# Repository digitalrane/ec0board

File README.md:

ec0board
========

ec0board is a personal project to replace the dead control board in my otherwise landfill Kogan TKL mechanical keyboard.
It was designed to occupy the exact same physical dimensions, and have the exact same key switch spacing as the original board, however has a much more powerful user-controlled MCU.
The MCU used is an AT90USB1286, chosen for the number of GPIOs, enabling NKRO to be achieved. It uses a diode matrix to connect the key switches, and takes Cherry-MX compatible key switches (I use browns).
Support is being added to the open source QMK firmware for this board, as the intention is to run a completely open keyboard replacement.

The board supports a switchable backlight, and additional RGB LED underneath the board (to see if the controller is alive, basically) and switchable backlights for the Fn, Caps, Scroll and Num lock keys independently to the main backlight.

This board uses custom footprints and 3d models for the following. If you find any of them missing from this repository, please file an issue.
* Cherry MX Brown switch model and footprint
* AT90USB1286 model and footprint
* Ingwaz rune (because I like to ensure runes or sigils cover my electronics for great ~ mystical power ~)

Versions
========

* v0: Original prototype, ended up not working reliably because I goofed the electron-herding aspects of this version.
* v1: Original replacement. Found the Micro USB connector to be flimsy, because Micro USB is a bit crap. Also had a testing RGB LED space,
  which never worked right. Other than that, fairly reliable, but still relied on the Kogan TKL or similar cheap Aliexpress/eBay donor KB.
* v2: Never released or manufactured, added standalone supports, rerouted entire keyboard to use newly added standard KiCad key switch
  footprints, generally cleaned up routing. Started moving toward a Mini USB connector to address connector stability.
* v3: Decided to use USB-C during a dream, so rewired the whole power supply and USB connection section. Further routing improvements.
  Cleaned up all footprints, values, and added better more descriptive values to components so a proper BOM could be generated. Generated a
  proper BOM with the Interactive HTML BOM KiCad plugin. Updated everything for KiCad 5.1 and added some more 3D models. All required
  libraries are now in KiCad or this repo.

Firmware
========

This keyboard uses QMK, and a board definition and configuration is included in the `qmk_ec0board` directory. Drop this into QMK and set
your keyboard type to 'ec0board' on the make commandline as documented [here](https://beta.docs.qmk.fm/detailed-guides/getting_started_make_guide).

e.g.:
`make ec0board`

Flashing
========

Programming of the firmware is done via the ISP header. You will need a standard AVR ISP programmer, I use an Olimex unit. They keyboard
should not be powered via USB whilst flashing, but you won't get magic smoke if you do it accidentally (yeah I tried it, so what, are you a
cop?).

Fuses
=====

The fuses on your AT90USB1286 should be set for external crystal oscillator operation, with JTAG disabled, to free up enough GPIOs. We
also want SPIEN set so we can use the ISP to flash/recover the chip.

The fules should be set to -
(E:F3, H:D9, L:DE)

BOM
===

Thanks to the wonderful [InteractiveHtmlBom](https://github.com/openscopeproject/InteractiveHtmlBom) KiCad plugin, this repository now
contains a really nice HTML BOM. You can clone this repo and browse it locally in the `bom` directory, or download/view it from
[here](https://rawcdn.githack.com/devec0/ec0board/master/bom/ibom.html).

For U1, AT90USB1286 is the sensible option, because no keyboard needs the host mode support of AT90USB1287.
If you need host mode, you're an absolute maniac. I want to know what you're up to, get in touch!

TODO
====

* Finish code for lighting backlight behind Capslock, Scrolllock, Numlock and the Function key when engaged
* Finish code to get the Function key working correctly

And another thing
=================

<3

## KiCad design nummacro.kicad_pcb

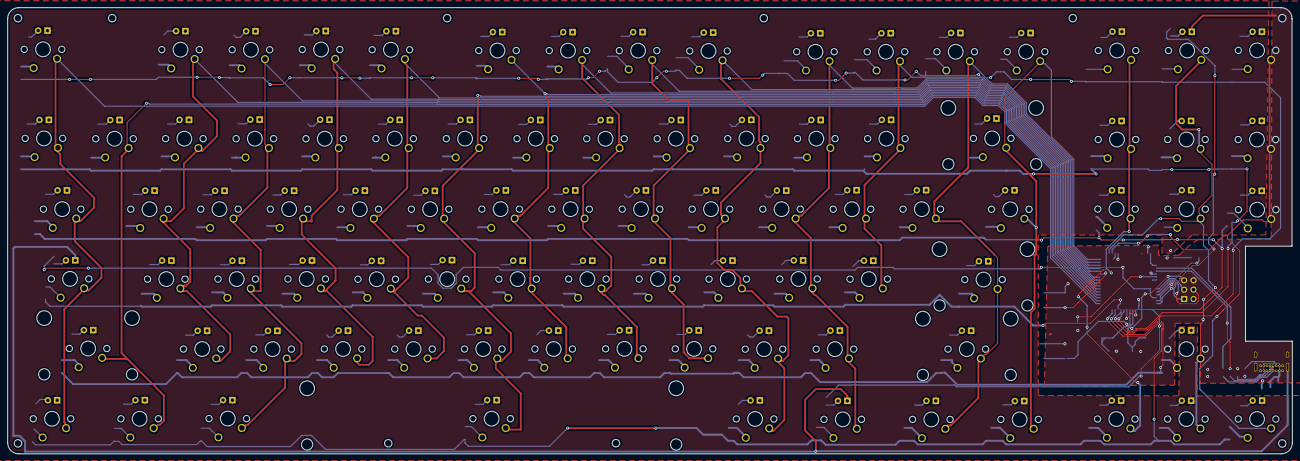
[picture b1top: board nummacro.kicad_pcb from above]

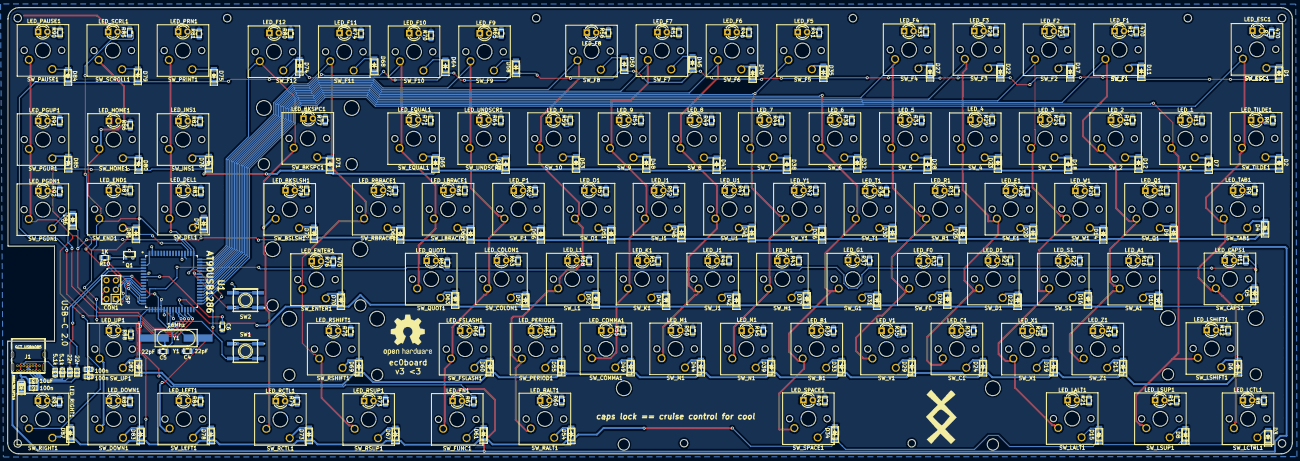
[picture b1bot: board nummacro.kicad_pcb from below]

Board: 2 copper layers, 348.1 x 120.9 mm, 368 parts (194 on the bottom side), 221 nets.

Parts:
C2, C3, C7: 100n; C_0805_2012Metric_Pad1.15x1.40mm_HandSolder
C4, C5: 22pF; C_0805_2012Metric_Pad1.15x1.40mm_HandSolder
C6: 1uF; C_0805_2012Metric_Pad1.15x1.40mm_HandSolder
C8: 10uF; C_0805_2012Metric_Pad1.15x1.40mm_HandSolder
CON1: ISP; PinHeader_2x03_P2.54mm_Vertical
D1, D2, D3, D4, D5, D6, D7, D8, D9, D10, D11, D12, D13, D14, D15, D16, D17, D18, D19, D20, D21, D22, D23, D24, D25, D26, D27, D28, D29, D30, D31, D32, D33, D34, D35, D36, D37, D38, D39, D40, D41, D42, D43, D44, D45, D46, D47, D48, D49, D50, D51, D52, D53, D54, D55, D56, D57, D58, D59, D60, D61, D62, D63, D64, D65, D66, D67, D68, D69, D70, D71, D72, D73, D74, D75, D76, D77, D78, D79, D80, D81, D82, D83, D84, D85, D86, D87: D; D_MiniMELF
D88: MBR130LSFT1G; D_PowerDI-123
J1: GCT USB4085; USB_C_Receptacle_GCT_USB4085
LED_0, LED_1, LED_2, LED_3, LED_4, LED_5, LED_6, LED_7, LED_8, LED_9: Led_Small; LED_D3.0mm
LED_A1: Led_Small; LED_D3.0mm
LED_B1: Led_Small; LED_D3.0mm
LED_BKSLSH1: Led_Small; LED_D3.0mm
LED_BKSPC1: Led_Small; LED_D3.0mm
LED_C1: Led_Small; LED_D3.0mm
LED_CAPS1: Led_Small; LED_D3.0mm
LED_COLON1: Led_Small; LED_D3.0mm
LED_COMMA1: Led_Small; LED_D3.0mm
LED_D1: Led_Small; LED_D3.0mm
LED_DEL1: Led_Small; LED_D3.0mm
LED_DOWN1: Led_Small; LED_D3.0mm
LED_E1: Led_Small; LED_D3.0mm
LED_END1: Led_Small; LED_D3.0mm
LED_ENTER1: Led_Small; LED_D3.0mm
LED_EQUAL1: Led_Small; LED_D3.0mm
LED_ESC1: ESC; LED_D3.0mm
LED_F0, LED_F1, LED_F2, LED_F3, LED_F4, LED_F5, LED_F6, LED_F7, LED_F8, LED_F9, LED_F10, LED_F11, LED_F12: Led_Small; LED_D3.0mm
LED_FN1: Led_Small; LED_D3.0mm
LED_FSLASH1: Led_Small; LED_D3.0mm
LED_G1: Led_Small; LED_D3.0mm
LED_H1: Led_Small; LED_D3.0mm
LED_HOME1: Led_Small; LED_D3.0mm
LED_I1: Led_Small; LED_D3.0mm
LED_INS1: Led_Small; LED_D3.0mm
LED_J1: Led_Small; LED_D3.0mm
LED_K1: Led_Small; LED_D3.0mm
LED_L1: Led_Small; LED_D3.0mm
LED_LALT1: Led_Small; LED_D3.0mm
LED_LBRACE1: Led_Small; LED_D3.0mm
LED_LCTL1: Led_Small; LED_D3.0mm
LED_LEFT1: Led_Small; LED_D3.0mm
LED_LSHIFT1: Led_Small; LED_D3.0mm
LED_LSUP1: Led_Small; LED_D3.0mm
LED_M1: Led_Small; LED_D3.0mm
LED_N1: Led_Small; LED_D3.0mm
LED_O1: Led_Small; LED_D3.0mm
LED_P1: Led_Small; LED_D3.0mm
LED_PAUSE1: Led_Small; LED_D3.0mm
LED_PERIOD1: Led_Small; LED_D3.0mm
LED_PGDN1: Led_Small; LED_D3.0mm
LED_PGUP1: Led_Small; LED_D3.0mm
LED_PRN1: Led_Small; LED_D3.0mm
LED_Q1: Led_Small; LED_D3.0mm
LED_QUOT1: Led_Small; LED_D3.0mm
LED_R1: Led_Small; LED_D3.0mm
LED_RALT1: Led_Small; LED_D3.0mm
LED_RBRACE1: Led_Small; LED_D3.0mm
LED_RCTL1: Led_Small; LED_D3.0mm
LED_RIGHT1: Led_Small; LED_D3.0mm
LED_RSHIFT1: Led_Small; LED_D3.0mm
LED_RSUP1: Led_Small; LED_D3.0mm
LED_S1: Led_Small; LED_D3.0mm
LED_SCRL1: Led_Small; LED_D3.0mm
LED_SPACE1: Led_Small; LED_D3.0mm
LED_T1: Led_Small; LED_D3.0mm
LED_TAB1: Led_Small; LED_D3.0mm
LED_TILDE1: Led_Small; LED_D3.0mm
LED_U1: Led_Small; LED_D3.0mm
LED_UNDSCR1: Led_Small; LED_D3.0mm
LED_UP1: Led_Small; LED_D3.0mm
LED_V1: Led_Small; LED_D3.0mm
LED_W1: Led_Small; LED_D3.0mm
LED_X1: Led_Small; LED_D3.0mm
LED_Y1: Led_Small; LED_D3.0mm
LED_Z1: Led_Small; LED_D3.0mm
Q1: Q_NPN_BEC; SOT-23
R2, R3: 5.1k; R_0805_2012Metric_Pad1.15x1.40mm_HandSolder
R4, R5: 22r; R_0805_2012Metric_Pad1.15x1.40mm_HandSolder
R6, R7, R8, R9, R11, R12, R13, R14, R15, R16, R17, R18, R19, R20, R21, R22, R23, R24, R25, R26, R27, R28, R29, R30, R31, R32, R33, R34, R35, R36, R37, R38, R39, R40, R41, R42, R43, R44, R45, R46, R47, R48, R49, R50, R51, R52, R53, R54, R55, R56, R57, R58, R59, R60, R61, R62, R63, R64, R65, R66, R67, R68, R69, R70, R71, R72, R73, R74, R75, R76, R77, R78, R79, R80, R81, R82, R83, R84, R85, R86, R87, R88, R89, R90, R91, R92, R93: 470; R_0805_2012Metric_Pad1.15x1.40mm_HandSolder
R10: 1K; R_0805_2012Metric_Pad1.15x1.40mm_HandSolder
SW1: SW_RESET; SW_SPST_EVQQ2
SW2: SW_HWB; SW_SPST_EVQQ2
SW_1, SW_3, SW_4, SW_5, SW_6, SW_7, SW_8, SW_9, SW_10: MX_LED; SW_Cherry_MX1A_1.00u_PCB
SW_2: 2; SW_Cherry_MX1A_1.00u_PCB
SW_A1: MX_LED; SW_Cherry_MX1A_1.00u_PCB
SW_B1: MX_LED; SW_Cherry_MX1A_1.00u_PCB
SW_BKSPC1: MX_LED; SW_Cherry_MX1A_2.00u_PCB
SW_BSLSH1: MX_LED; SW_Cherry_MX1A_1.50u_PCB
SW_C1: MX_LED; SW_Cherry_MX1A_1.00u_PCB
SW_CAPS1: MX_LED; SW_Cherry_MX1A_1.75u_PCB
SW_COLON1: MX_LED; SW_Cherry_MX1A_1.00u_PCB
SW_COMMA1: MX_LED; SW_Cherry_MX1A_1.00u_PCB
SW_D1: MX_LED; SW_Cherry_MX1A_1.00u_PCB
SW_DEL1: MX_LED; SW_Cherry_MX1A_1.00u_PCB
SW_DOWN1: MX_LED; SW_Cherry_MX1A_1.00u_PCB
SW_E1: MX_LED; SW_Cherry_MX1A_1.00u_PCB
SW_END1: MX_LED; SW_Cherry_MX1A_1.00u_PCB
SW_ENTER1: MX_LED; SW_Cherry_MX1A_2.25u_PCB
SW_EQUAL1: MX_LED; SW_Cherry_MX1A_1.00u_PCB
SW_ESC1: MX_LED; SW_Cherry_MX1A_1.00u_PCB
SW_F0, SW_F1, SW_F2, SW_F3, SW_F4, SW_F5, SW_F6, SW_F7, SW_F8, SW_F9, SW_F10, SW_F11, SW_F12: MX_LED; SW_Cherry_MX1A_1.00u_PCB
SW_FSLASH1: MX_LED; SW_Cherry_MX1A_1.00u_PCB
SW_FUNC1: MX_LED; SW_Cherry_MX1A_1.25u_PCB
SW_G1: MX_LED; SW_Cherry_MX1A_1.00u_PCB
SW_H1: MX_LED; SW_Cherry_MX1A_1.00u_PCB
SW_HOME1: MX_LED; SW_Cherry_MX1A_1.00u_PCB
SW_I1: MX_LED; SW_Cherry_MX1A_1.00u_PCB
SW_INS1: MX_LED; SW_Cherry_MX1A_1.00u_PCB
SW_J1: MX_LED; SW_Cherry_MX1A_1.00u_PCB
SW_K1: MX_LED; SW_Cherry_MX1A_1.00u_PCB
SW_L1: MX_LED; SW_Cherry_MX1A_1.00u_PCB
SW_LALT1: MX_LED; SW_Cherry_MX1A_1.25u_PCB
SW_LBRACE1: MX_LED; SW_Cherry_MX1A_1.00u_PCB
SW_LCTRL1: MX_LED; SW_Cherry_MX1A_1.25u_PCB
SW_LEFT1: MX_LED; SW_Cherry_MX1A_1.00u_PCB
SW_LSHIFT1: MX_LED; SW_Cherry_MX1A_2.25u_PCB
SW_LSUP1: MX_LED; SW_Cherry_MX1A_1.25u_PCB
SW_M1: MX_LED; SW_Cherry_MX1A_1.00u_PCB
SW_N1: MX_LED; SW_Cherry_MX1A_1.00u_PCB
SW_O1: MX_LED; SW_Cherry_MX1A_1.00u_PCB
SW_P1: MX_LED; SW_Cherry_MX1A_1.00u_PCB
SW_PAUSE1: MX_LED; SW_Cherry_MX1A_1.00u_PCB
SW_PERIOD1: MX_LED; SW_Cherry_MX1A_1.00u_PCB
SW_PGDN1: MX_LED; SW_Cherry_MX1A_1.00u_PCB
SW_PGUP1: MX_LED; SW_Cherry_MX1A_1.00u_PCB
SW_PRINT1: MX_LED; SW_Cherry_MX1A_1.00u_PCB
SW_Q1: MX_LED; SW_Cherry_MX1A_1.00u_PCB
SW_QUOT1: MX_LED; SW_Cherry_MX1A_1.00u_PCB
SW_R1: MX_LED; SW_Cherry_MX1A_1.00u_PCB
SW_RALT1: MX_LED; SW_Cherry_MX1A_1.25u_PCB
SW_RBRACE1: MX_LED; SW_Cherry_MX1A_1.00u_PCB
SW_RCTL1: MX_LED; SW_Cherry_MX1A_1.25u_PCB
SW_RIGHT1: MX_LED; SW_Cherry_MX1A_1.00u_PCB
SW_RSHIFT1: MX_LED; SW_Cherry_MX1A_2.75u_PCB
SW_RSUP1: MX_LED; SW_Cherry_MX1A_1.25u_PCB
SW_S1: MX_LED; SW_Cherry_MX1A_1.00u_PCB
SW_SCROLL1: MX_LED; SW_Cherry_MX1A_1.00u_PCB
SW_SPACE1: MX_LED; SW_Cherry_MX1A_6.25u_PCB
SW_T1: MX_LED; SW_Cherry_MX1A_1.00u_PCB
SW_TAB1: MX_LED; SW_Cherry_MX1A_1.50u_PCB
SW_TILDE1: MX_LED; SW_Cherry_MX1A_1.00u_PCB
SW_U1: MX_LED; SW_Cherry_MX1A_1.00u_PCB
SW_UNDSCR1: MX_LED; SW_Cherry_MX1A_1.00u_PCB
SW_UP1: MX_LED; SW_Cherry_MX1A_1.00u_PCB
SW_V1: MX_LED; SW_Cherry_MX1A_1.00u_PCB
SW_W1: MX_LED; SW_Cherry_MX1A_1.00u_PCB
SW_X1: MX_LED; SW_Cherry_MX1A_1.00u_PCB
SW_Y1: MX_LED; SW_Cherry_MX1A_1.00u_PCB
SW_Z1: MX_LED; SW_Cherry_MX1A_1.00u_PCB
U1: AT90USB1286; QFP80P1600X1600X120-64N
Y1: 16Mhz; Crystal_SMD_HC49-SD_HandSoldering

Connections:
/controller/CUSB+: R5.1, U1.5
/controller/CUSB-: R4.1, U1.4
/controller/HWB: SW2.1, U1.43
/controller/MISO: CON1.1, U1.13
/controller/MOSI: CON1.4, U1.12
/controller/SCK: CON1.3, U1.11
/controller/UCAP: C6.1, U1.7
/controller/USB+: J1.A6, J1.B6, R5.2
/controller/USB-: J1.A7, J1.B7, R4.2
/controller/XTAL1: C4.1, U1.24, Y1.1
/controller/XTAL2: C5.1, U1.23, Y1.2
BL: R10.2, U1.15
BLGND: LED_0.1, LED_1.1, LED_2.1, LED_3.1, LED_4.1, LED_5.1, LED_6.1, LED_7.1, LED_8.1, LED_9.1, LED_A1.1, LED_B1.1, LED_BKSLSH1.1, LED_BKSPC1.1, LED_C1.1, LED_COLON1.1, LED_COMMA1.1, LED_D1.1, LED_DEL1.1, LED_DOWN1.1, LED_E1.1, LED_END1.1, LED_ENTER1.1, LED_EQUAL1.1, LED_ESC1.1, LED_F0.1, LED_F1.1, LED_F2.1, LED_F3.1, LED_F4.1, LED_F5.1, LED_F6.1, LED_F7.1, LED_F8.1, LED_F9.1, LED_F10.1, LED_F11.1, LED_F12.1, LED_FSLASH1.1, LED_G1.1, LED_H1.1, LED_HOME1.1, LED_I1.1, LED_INS1.1, LED_J1.1, LED_K1.1, LED_L1.1, LED_LALT1.1, LED_LBRACE1.1, LED_LCTL1.1, LED_LEFT1.1, LED_LSHIFT1.1, LED_LSUP1.1, LED_M1.1, LED_N1.1, LED_O1.1, LED_P1.1, LED_PAUSE1.1, LED_PERIOD1.1, LED_PGDN1.1, LED_PGUP1.1, LED_PRN1.1, LED_Q1.1, LED_QUOT1.1, LED_R1.1, LED_RALT1.1, LED_RBRACE1.1, LED_RCTL1.1, LED_RIGHT1.1, LED_RSHIFT1.1, LED_RSUP1.1, LED_S1.1, LED_SPACE1.1, LED_T1.1, LED_TAB1.1, LED_TILDE1.1, LED_U1.1, LED_UNDSCR1.1, LED_UP1.1, LED_V1.1, LED_W1.1, LED_X1.1, LED_Y1.1, LED_Z1.1, Q1.3
CapsBL: R11.2, U1.14
Col1: SW_CAPS1.2, SW_ESC1.2, SW_LCTRL1.2, SW_TAB1.2, SW_TILDE1.2, U1.33
Col2: SW_1.2, SW_LSHIFT1.2, SW_LSUP1.2, U1.34
Col3: SW_2.2, SW_A1.2, SW_F1.2, SW_Q1.2, SW_Z1.2, U1.35
Col4: SW_3.2, SW_F2.2, SW_LALT1.2, SW_S1.2, SW_W1.2, SW_X1.2, U1.36
Col5: SW_4.2, SW_C1.2, SW_D1.2, SW_E1.2, SW_F3.2, U1.37
Col6: SW_5.2, SW_F0.2, SW_F4.2, SW_R1.2, SW_V1.2, U1.38
Col7: SW_6.2, SW_B1.2, SW_G1.2, SW_SPACE1.2, SW_T1.2, U1.39
Col8: SW_7.2, SW_F5.2, SW_H1.2, SW_N1.2, SW_Y1.2, U1.40
Col9: SW_8.2, SW_F6.2, SW_J1.2, SW_M1.2, SW_U1.2, U1.41
Col10: SW_9.2, SW_COMMA1.2, SW_F7.2, SW_I1.2, SW_K1.2, U1.42
Col11: SW_10.2, SW_F8.2, SW_L1.2, SW_O1.2, SW_PERIOD1.2, SW_RALT1.2, U1.44
Col12: SW_COLON1.2, SW_F9.2, SW_FSLASH1.2, SW_FUNC1.2, SW_P1.2, SW_UNDSCR1.2, U1.45
Col13: SW_EQUAL1.2, SW_F10.2, SW_LBRACE1.2, SW_QUOT1.2, U1.46
Col14: SW_ENTER1.2, SW_F11.2, SW_RBRACE1.2, SW_RSHIFT1.2, SW_RSUP1.2, U1.47
Col15: SW_BKSPC1.2, SW_BSLSH1.2, SW_F12.2, SW_RCTL1.2, U1.48
Col16: SW_DEL1.2, SW_INS1.2, SW_LEFT1.2, SW_PRINT1.2, U1.49
Col17: SW_DOWN1.2, SW_END1.2, SW_HOME1.2, SW_SCROLL1.2, SW_UP1.2, U1.50
Col18: SW_PAUSE1.2, SW_PGDN1.2, SW_PGUP1.2, SW_RIGHT1.2, U1.51
FnBL: R67.2, U1.17
GND: C2.2, C3.2, C4.2, C5.2, C6.2, C7.2, C8.1, CON1.6, J1.A1, J1.A12, J1.B1, J1.B12, J1.S1, LED_CAPS1.1, LED_FN1.1, LED_SCRL1.1, Q1.2, R2.1, R3.1, SW1.1, SW2.2, U1.6, U1.22, U1.53, U1.63
unnamed: D1.2, SW_ESC1.1
unnamed: D2.2, SW_TILDE1.1
unnamed: D3.2, SW_LCTRL1.1
unnamed: D4.2, SW_TAB1.1
unnamed: D5.2, SW_CAPS1.1
unnamed: D6.2, SW_LSHIFT1.1
unnamed: D7.2, SW_1.1
unnamed: D8.2, SW_LSUP1.1
unnamed: D9.2, SW_Q1.1
unnamed: D10.2, SW_A1.1
unnamed: D11.2, SW_F1.1
unnamed: D12.2, SW_2.1
unnamed: D13.2, SW_Z1.1
unnamed: D14.2, SW_W1.1
unnamed: D15.2, SW_LALT1.1
unnamed: D16.2, SW_S1.1
unnamed: D17.2, SW_F2.1
unnamed: D18.2, SW_3.1
unnamed: D19.2, SW_X1.1
unnamed: D20.2, SW_E1.1
unnamed: D21.2, SW_D1.1
unnamed: D22.2, SW_F3.1
unnamed: D23.2, SW_4.1
unnamed: D24.2, SW_C1.1
unnamed: D25.2, SW_R1.1
unnamed: D26.2, SW_F0.1
unnamed: D27.2, SW_F4.1
unnamed: D28.2, SW_5.1
unnamed: D29.2, SW_V1.1
unnamed: D30.2, SW_T1.1
unnamed: D31.2, SW_G1.1
unnamed: D32.2, SW_6.1
unnamed: D33.2, SW_B1.1
unnamed: D34.2, SW_SPACE1.1
unnamed: D35.2, SW_F5.1
unnamed: D36.2, SW_Y1.1
unnamed: D37.2, SW_H1.1
unnamed: D38.2, SW_7.1
unnamed: D39.2, SW_N1.1
unnamed: D40.2, SW_F6.1
unnamed: D41.2, SW_U1.1
unnamed: D42.2, SW_J1.1
unnamed: D43.2, SW_8.1
unnamed: D44.2, SW_M1.1
unnamed: D45.2, SW_F7.1
unnamed: D46.2, SW_I1.1
unnamed: D47.2, SW_K1.1
unnamed: D48.2, SW_9.1
unnamed: D49.2, SW_COMMA1.1
unnamed: D50.2, SW_F8.1
unnamed: D51.2, SW_O1.1
unnamed: D52.2, SW_L1.1
unnamed: D53.2, SW_10.1
unnamed: D54.2, SW_RALT1.1
unnamed: D55.2, SW_PERIOD1.1
unnamed: D56.2, SW_P1.1
unnamed: D57.2, SW_COLON1.1
unnamed: D58.2, SW_F9.1
unnamed: D59.2, SW_UNDSCR1.1
unnamed: D60.2, SW_FSLASH1.1
unnamed: D61.2, SW_FUNC1.1
unnamed: D62.2, SW_LBRACE1.1
unnamed: D63.2, SW_QUOT1.1
unnamed: D64.2, SW_F10.1
unnamed: D65.2, SW_EQUAL1.1
unnamed: D66.2, SW_RBRACE1.1
unnamed: D67.2, SW_RSUP1.1
unnamed: D68.2, SW_F11.1
unnamed: D69.2, SW_RSHIFT1.1
unnamed: D70.2, SW_ENTER1.1
unnamed: D71.2, SW_BKSPC1.1
unnamed: D72.2, SW_BSLSH1.1
unnamed: D73.2, SW_RCTL1.1
unnamed: D74.2, SW_F12.1
unnamed: D75.2, SW_PRINT1.1
unnamed: D76.2, SW_INS1.1
unnamed: D77.2, SW_DEL1.1
unnamed: D78.2, SW_LEFT1.1
unnamed: D79.2, SW_SCROLL1.1
unnamed: D80.2, SW_HOME1.1
unnamed: D81.2, SW_END1.1
unnamed: D82.2, SW_UP1.1
unnamed: D83.2, SW_DOWN1.1
unnamed: D84.2, SW_PAUSE1.1
unnamed: D85.2, SW_PGUP1.1
unnamed: D86.2, SW_PGDN1.1
unnamed: D87.2, SW_RIGHT1.1
unnamed: J1.A5, R2.2
unnamed: J1.B5, R3.2
unnamed: LED_0.2, R59.1
unnamed: LED_1.2, R13.1
unnamed: LED_2.2, R18.1
unnamed: LED_3.2, R24.1
unnamed: LED_4.2, R29.1
unnamed: LED_5.2, R34.1
unnamed: LED_6.2, R38.1
unnamed: LED_7.2, R44.1
unnamed: LED_8.2, R49.1
unnamed: LED_9.2, R54.1
unnamed: LED_A1.2, R16.1
unnamed: LED_B1.2, R39.1
unnamed: LED_BKSLSH1.2, R78.1
unnamed: LED_BKSPC1.2, R77.1
unnamed: LED_C1.2, R30.1
unnamed: LED_CAPS1.2, R11.1
unnamed: LED_COLON1.2, R63.1
unnamed: LED_COMMA1.2, R55.1
unnamed: LED_D1.2, R27.1
unnamed: LED_DEL1.2, R83.1
unnamed: LED_DOWN1.2, R89.1
unnamed: LED_E1.2, R26.1
unnamed: LED_END1.2, R87.1
unnamed: LED_ENTER1.2, R76.1
unnamed: LED_EQUAL1.2, R71.1
unnamed: LED_ESC1.2, R7.1
unnamed: LED_F0.2, R32.1
unnamed: LED_F1.2, R17.1
unnamed: LED_F2.2, R23.1
unnamed: LED_F3.2, R28.1
unnamed: LED_F4.2, R33.1
unnamed: LED_F5.2, R41.1
unnamed: LED_F6.2, R46.1
unnamed: LED_F7.2, R51.1
unnamed: LED_F8.2, R56.1
unnamed: LED_F9.2, R65.1
unnamed: LED_F10.2, R70.1
unnamed: LED_F11.2, R74.1
unnamed: LED_F12.2, R80.1
unnamed: LED_FN1.2, R67.1
unnamed: LED_FSLASH1.2, R66.1
unnamed: LED_G1.2, R37.1
unnamed: LED_H1.2, R43.1
unnamed: LED_HOME1.2, R86.1
unnamed: LED_I1.2, R52.1
unnamed: LED_INS1.2, R82.1
unnamed: LED_J1.2, R48.1
unnamed: LED_K1.2, R53.1
unnamed: LED_L1.2, R58.1
unnamed: LED_LALT1.2, R21.1
unnamed: LED_LBRACE1.2, R68.1
unnamed: LED_LCTL1.2, R8.1
unnamed: LED_LEFT1.2, R84.1
unnamed: LED_LSHIFT1.2, R12.1
unnamed: LED_LSUP1.2, R14.1
unnamed: LED_M1.2, R50.1
unnamed: LED_N1.2, R45.1
unnamed: LED_O1.2, R57.1
unnamed: LED_P1.2, R62.1
unnamed: LED_PAUSE1.2, R90.1
unnamed: LED_PERIOD1.2, R61.1
unnamed: LED_PGDN1.2, R92.1
unnamed: LED_PGUP1.2, R91.1
unnamed: LED_PRN1.2, R81.1
unnamed: LED_Q1.2, R15.1
unnamed: LED_QUOT1.2, R69.1
unnamed: LED_R1.2, R31.1
unnamed: LED_RALT1.2, R60.1
unnamed: LED_RBRACE1.2, R72.1
unnamed: LED_RCTL1.2, R79.1
unnamed: LED_RIGHT1.2, R93.1
unnamed: LED_RSHIFT1.2, R75.1
unnamed: LED_RSUP1.2, R73.1
unnamed: LED_S1.2, R22.1
unnamed: LED_SCRL1.2, R85.1
unnamed: LED_SPACE1.2, R40.1
unnamed: LED_T1.2, R36.1
unnamed: LED_TAB1.2, R9.1
unnamed: LED_TILDE1.2, R6.1
unnamed: LED_U1.2, R47.1
unnamed: LED_UNDSCR1.2, R64.1
unnamed: LED_UP1.2, R88.1
unnamed: LED_V1.2, R35.1
unnamed: LED_W1.2, R20.1
unnamed: LED_X1.2, R25.1
unnamed: LED_Y1.2, R42.1
unnamed: LED_Z1.2, R19.1
unnamed: Q1.1, R10.1
RESET: CON1.5, SW1.2, U1.20
Row1: D1.1, D11.1, D17.1, D22.1, D27.1, D35.1, D40.1, D45.1, D50.1, D58.1, D64.1, D68.1, D74.1, D75.1, D79.1, D84.1, U1.27
Row2: D2.1, D7.1, D12.1, D18.1, D23.1, D28.1, D32.1, D38.1, D43.1, D48.1, D53.1, D59.1, D65.1, D71.1, D76.1, D80.1, D85.1, U1.26
Row3: D4.1, D9.1, D14.1, D20.1, D25.1, D30.1, D36.1, D41.1, D46.1, D51.1, D56.1, D62.1, D66.1, D72.1, D77.1, D81.1, D86.1, U1.25
Row4: D5.1, D10.1, D16.1, D21.1, D26.1, D31.1, D37.1, D42.1, D47.1, D52.1, D57.1, D63.1, D70.1, U1.28
Row5: D6.1, D13.1, D19.1, D24.1, D29.1, D33.1, D39.1, D44.1, D49.1, D55.1, D60.1, D69.1, D82.1, U1.29
Row6: D3.1, D8.1, D15.1, D34.1, D54.1, D61.1, D67.1, D73.1, D78.1, D83.1, D87.1, U1.30
ScrollBL: R85.2, U1.16
VBUS: C7.1, C8.2, D88.2, J1.A4, J1.A9, J1.B4, J1.B9
VCC: C2.1, C3.1, CON1.2, D88.1, R6.2, R7.2, R8.2, R9.2, R12.2, R13.2, R14.2, R15.2, R16.2, R17.2, R18.2, R19.2, R20.2, R21.2, R22.2, R23.2, R24.2, R25.2, R26.2, R27.2, R28.2, R29.2, R30.2, R31.2, R32.2, R33.2, R34.2, R35.2, R36.2, R37.2, R38.2, R39.2, R40.2, R41.2, R42.2, R43.2, R44.2, R45.2, R46.2, R47.2, R48.2, R49.2, R50.2, R51.2, R52.2, R53.2, R54.2, R55.2, R56.2, R57.2, R58.2, R59.2, R60.2, R61.2, R62.2, R63.2, R64.2, R65.2, R66.2, R68.2, R69.2, R70.2, R71.2, R72.2, R73.2, R74.2, R75.2, R76.2, R77.2, R78.2, R79.2, R80.2, R81.2, R82.2, R83.2, R84.2, R86.2, R87.2, R88.2, R89.2, R90.2, R91.2, R92.2, R93.2, U1.3, U1.8, U1.21, U1.52, U1.64

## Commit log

2018-09-17 Initial commit of v2 ec0board
2018-09-17 Added BOM and README
2018-09-17 Fixed table formatting for BOM
2018-09-17 Added QMK board files
2018-09-17 Added fuse info
2019-05-25 Moved to stock KiCad MX buttons and LEDs, cleaned up routing, added a USB-C connection to replace the flimsy Micro-USB, Updated for latest KiCad
2019-08-31 Rerouted, migrated to standard KiCad keyboard footprints, moved to USB-C to address durability issues. Added holed for PCB-mounted stabilisers for standalone usage.
2019-08-31 Updated drill and pos files
2019-08-31 Start ignoring zip files
2019-08-31 Regenerated all gerbers and drill files, removed duplicates
2019-08-31 WIP USB-C 3d model, cleaned up main key matrix routing quite a bit
2019-08-31 Silkscreen overhaul to move everything to the back layer, moved diode symbols to silkscreen from fab layer. Regenerated gerbs.
2019-10-07 v3 initial commit, USB-C, interactive BOM, rerouted and changed to use standard KiCad libs where possible
2019-10-07 v3 Gerbers
